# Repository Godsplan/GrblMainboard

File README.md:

GrblMainboard - v3.1
=============

A new Solution with Grbl Firmware to use cnc mills or 3d printers.

created by Christoph Kielhorn (Godsplan), Frank Herrmann (xpix)

---------------

The GrblMainboard includes the following features:

- ATMega328u (DIL Package)
- USB Connection using USB-FTDI
- Opto-Couplers for USB Connection
- ICSP-Connector for flashing the firmware
- GRBL Firmware (v0.8) and GRBL Pinout
- Connector for External Buttons for spindle, reset, etc...
- Support for four Pololu A4988 or Pololu DRV8825 Modules
- Supports dual-Y motion
- Supports cooling fan
- Supports XYZ-Limit in extra pinheader
- LED's for every axis
- LED's for every Limit
- Power LED
- AK500 Screw terminal for Steppers
- Connector for Bluetooth TTL Modules

---------------
v3.1
- Added Hall Sensor Pinout

v3.0 - GrblMainboard Backfork
- Added Pin Locations
- Added I2C Connectors for Sensors

v0.9.1 - XStepper Development

- add optional pullup resistors (1k/5V) for Hallo Sesnor switches (Cherry MP101401)
   http://www.cherrycorp.com/english/sensors/pdf/MP1014_Series.pdf

v0.9 - Initial Development

- created schema files
- created .brd

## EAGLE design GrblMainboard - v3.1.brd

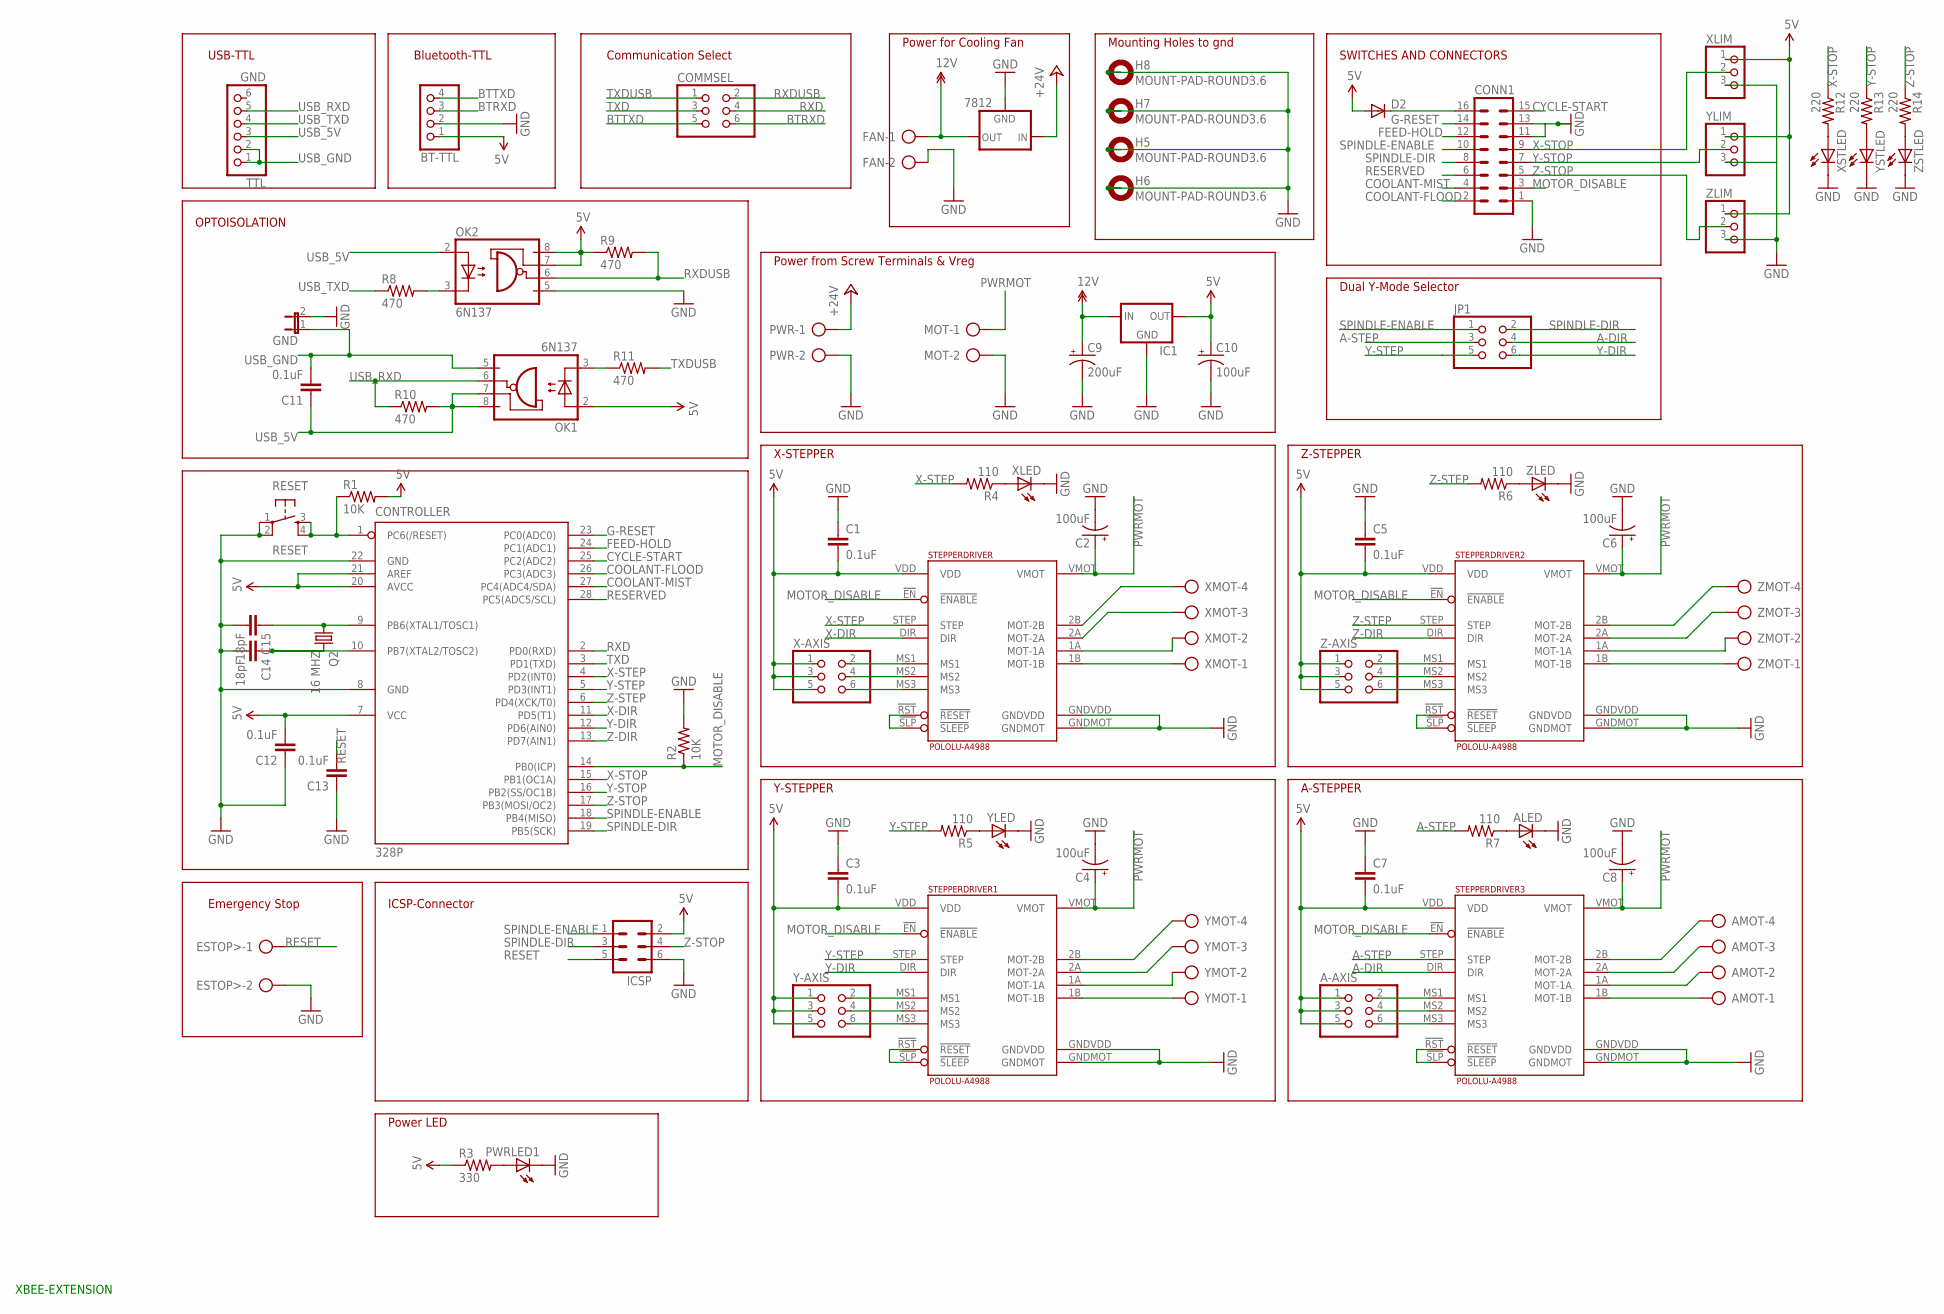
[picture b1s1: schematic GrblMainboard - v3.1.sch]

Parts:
328P: CONTROLLER; DIL28-3
7812: V_REG_78XXSINK; TO220-IGO
A-AXIS: PINHD-2X3; 2X03
ALED: LED3MM
AMOT: AK500/4
BT-TTL: PINHD-1X4; 1X04
C1, C3, C5, C7, C11, C12, C13: 0.1uF; C025-025X050
C2, C4, C6, C8: 100uF; E3,5-8
C9: 200uF; E2,5-6
C10: 100uF; E2,5-6
C14, C15: 18pF; C025-025X050
COMMSEL: PINHD-2X3; 2X03
CONN1: ML16
D2: DIODEPTH; DIODE-1N4001
ESTOP>: AK500/2
FAN: AK500/2
GND: JP1E; JP1
H5, H6, H7, H8: MOUNT-PAD-ROUND3.6; 3,6-PAD
IC1: V_REG_78XXSINK; TO220-IGO
ICSP: ML6
JP1: PINHD-2X3; 2X03
MOT: AK500/2
OK1, OK2: 6N137; DIL08
PWR: AK500/2
PWRLED1: LED3MM
Q2: 16 MHZ; HC49/S
R1, R2: 10K; AXIAL-0.3
R3: 330; 1/6W-RES
R4, R5, R6, R7: 110; AXIAL-0.3
R8, R9, R10, R11: 470; AXIAL-0.3
R12, R13, R14: 220; AXIAL-0.3
RESET: RESET; TACTILE-PTH
STEPPERDRIVER, STEPPERDRIVER1, STEPPERDRIVER2, STEPPERDRIVER3: POLOLU-A4988; POLOLU-ALLEGRO-PTH
TTL: GND; 1X06
X-AXIS: PINHD-2X3; 2X03
XLED: LED3MM
XLIM: PINHD-1X3; 1X03
XMOT: AK500/4
XSTLED: LED3MM
Y-AXIS: PINHD-2X3; 2X03
YLED: LED3MM
YLIM: PINHD-1X3; 1X03
YMOT: AK500/4
YSTLED: LED3MM
Z-AXIS: PINHD-2X3; 2X03
ZLED: LED3MM
ZLIM: PINHD-1X3; 1X03
ZMOT: AK500/4
ZSTLED: LED3MM

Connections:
5V: 328P.7 (VCC), 328P.20 (AVCC), 328P.21 (AREF), A-AXIS.1, A-AXIS.3, A-AXIS.5, BT-TTL.1, C1.2, C3.2, C5.2, C7.2, C10.+, C12.2, D2.A, IC1.OUT, ICSP.2, OK1.2 (A), OK2.7 (VE), OK2.8 (VCC), R1.P$2 (2), R3.1, R9.P$1 (1), STEPPERDRIVER.VDD, STEPPERDRIVER1.VDD, STEPPERDRIVER2.VDD, STEPPERDRIVER3.VDD, X-AXIS.1, X-AXIS.3, X-AXIS.5, XLIM.1, Y-AXIS.1, Y-AXIS.3, Y-AXIS.5, YLIM.1, Z-AXIS.1, Z-AXIS.3, Z-AXIS.5, ZLIM.1
12V: 7812.OUT, C9.+, FAN.1, IC1.IN
+24V: 7812.IN, PWR.1
A-DIR: JP1.4, STEPPERDRIVER3.DIR
A-STEP: JP1.3, R7.P$2 (2), STEPPERDRIVER3.STEP
BTRXD: BT-TTL.3, COMMSEL.6
BTTXD: BT-TTL.4, COMMSEL.5
COOLANT-FLOOD: 328P.26 (PC3(ADC3)), CONN1.2
COOLANT-MIST: 328P.27 (PC4(ADC4/SDA)), CONN1.4
CYCLE-START: 328P.25 (PC2(ADC2)), CONN1.15
FEED-HOLD: 328P.24 (PC1(ADC1)), CONN1.12
G-RESET: 328P.23 (PC0(ADC0)), CONN1.14
GND: 328P.8 (GND), 328P.22 (GND), 7812.GND, ALED.K (C), BT-TTL.2, C1.1, C2.-, C3.1, C4.-, C5.1, C6.-, C7.1, C8.-, C9.-, C10.-, C12.1, C13.1, C14.2, C15.2, CONN1.1, CONN1.11, CONN1.13, ESTOP>.2, FAN.2, GND.2, H5.B3,6, H6.B3,6, H7.B3,6, H8.B3,6, IC1.GND, ICSP.6, MOT.2, OK2.5 (GND), PWR.2, PWRLED1.K (C), R2.P$2 (2), RESET.1, RESET.2, STEPPERDRIVER.GNDMOT, STEPPERDRIVER.GNDVDD, STEPPERDRIVER1.GNDMOT, STEPPERDRIVER1.GNDVDD, STEPPERDRIVER2.GNDMOT, STEPPERDRIVER2.GNDVDD, STEPPERDRIVER3.GNDMOT, STEPPERDRIVER3.GNDVDD, XLED.K (C), XLIM.3, XSTLED.K (C), YLED.K (C), YLIM.3, YSTLED.K (C), ZLED.K (C), ZLIM.3, ZSTLED.K (C)
MOTOR_DISABLE: 328P.14 (PB0(ICP)), CONN1.3, R2.P$1 (1), STEPPERDRIVER.!EN (!ENABLE), STEPPERDRIVER1.!EN (!ENABLE), STEPPERDRIVER2.!EN (!ENABLE), STEPPERDRIVER3.!EN (!ENABLE)
unnamed: STEPPERDRIVER.1B (MOT-1B), XMOT.1
unnamed: STEPPERDRIVER.1A (MOT-1A), XMOT.2
unnamed: STEPPERDRIVER.2A (MOT-2A), XMOT.3
unnamed: STEPPERDRIVER.2B (MOT-2B), XMOT.4
unnamed: STEPPERDRIVER.!RST (!RESET), STEPPERDRIVER.!SLP (!SLEEP)
unnamed: STEPPERDRIVER.MS1, X-AXIS.2
unnamed: STEPPERDRIVER.MS2, X-AXIS.4
unnamed: STEPPERDRIVER.MS3, X-AXIS.6
unnamed: STEPPERDRIVER1.1B (MOT-1B), YMOT.1
unnamed: STEPPERDRIVER1.1A (MOT-1A), YMOT.2
unnamed: STEPPERDRIVER1.2A (MOT-2A), YMOT.3
unnamed: STEPPERDRIVER1.2B (MOT-2B), YMOT.4
unnamed: STEPPERDRIVER1.!RST (!RESET), STEPPERDRIVER1.!SLP (!SLEEP)
unnamed: STEPPERDRIVER1.MS1, Y-AXIS.2
unnamed: STEPPERDRIVER1.MS2, Y-AXIS.4
unnamed: STEPPERDRIVER1.MS3, Y-AXIS.6
unnamed: STEPPERDRIVER2.2B (MOT-2B), ZMOT.4
unnamed: STEPPERDRIVER2.2A (MOT-2A), ZMOT.3
unnamed: STEPPERDRIVER2.1A (MOT-1A), ZMOT.2
unnamed: STEPPERDRIVER2.1B (MOT-1B), ZMOT.1
unnamed: STEPPERDRIVER2.!RST (!RESET), STEPPERDRIVER2.!SLP (!SLEEP)
unnamed: STEPPERDRIVER2.MS1, Z-AXIS.2
unnamed: STEPPERDRIVER2.MS2, Z-AXIS.4
unnamed: STEPPERDRIVER2.MS3, Z-AXIS.6
unnamed: AMOT.1, STEPPERDRIVER3.1B (MOT-1B)
unnamed: AMOT.2, STEPPERDRIVER3.1A (MOT-1A)
unnamed: AMOT.3, STEPPERDRIVER3.2A (MOT-2A)
unnamed: AMOT.4, STEPPERDRIVER3.2B (MOT-2B)
unnamed: STEPPERDRIVER3.!RST (!RESET), STEPPERDRIVER3.!SLP (!SLEEP)
unnamed: A-AXIS.2, STEPPERDRIVER3.MS1
unnamed: A-AXIS.4, STEPPERDRIVER3.MS2
unnamed: A-AXIS.6, STEPPERDRIVER3.MS3
unnamed: 328P.9 (PB6(XTAL1/TOSC1)), C15.1, Q2.1
unnamed: 328P.10 (PB7(XTAL2/TOSC2)), C14.1, Q2.2
unnamed: OK2.3 (C), R8.P$2 (2)
unnamed: OK1.3 (C), R11.P$1 (1)
unnamed: R12.P$2 (2), XSTLED.A
unnamed: R4.P$1 (1), XLED.A
unnamed: R5.P$1 (1), YLED.A
unnamed: R6.P$1 (1), ZLED.A
unnamed: ALED.A, R7.P$1 (1)
unnamed: R13.P$2 (2), YSTLED.A
unnamed: PWRLED1.A, R3.2
unnamed: R14.P$2 (2), ZSTLED.A
unnamed: CONN1.16, D2.C
PWRMOT: C2.+, C4.+, C6.+, C8.+, MOT.1, STEPPERDRIVER.VMOT, STEPPERDRIVER1.VMOT, STEPPERDRIVER2.VMOT, STEPPERDRIVER3.VMOT
RESERVED: 328P.28 (PC5(ADC5/SCL)), CONN1.6
RESET: 328P.1 (PC6(/RESET)), C13.2, ESTOP>.1, ICSP.5, R1.P$1 (1), RESET.3, RESET.4
RXD: 328P.2 (PD0(RXD)), COMMSEL.4
RXDUSB: COMMSEL.2, OK2.6 (VO), R9.P$2 (2)
SPINDLE-DIR: 328P.19 (PB5(SCK)), CONN1.8, ICSP.3, JP1.2
SPINDLE-ENABLE: 328P.18 (PB4(MISO)), CONN1.10, ICSP.1, JP1.1
TXD: 328P.3 (PD1(TXD)), COMMSEL.3
TXDUSB: COMMSEL.1, R11.P$2 (2)
USB_5V: C11.1, OK1.7 (VE), OK1.8 (VCC), OK2.2 (A), R10.P$2 (2), TTL.3
USB_GND: C11.2, GND.1, OK1.5 (GND), TTL.1, TTL.2
USB_RXD: OK1.6 (VO), R10.P$1 (1), TTL.5
USB_TXD: R8.P$1 (1), TTL.4
X-DIR: 328P.11 (PD5(T1)), STEPPERDRIVER.DIR
X-STEP: 328P.4 (PD2(INT0)), R4.P$2 (2), STEPPERDRIVER.STEP
X-STOP: 328P.15 (PB1(OC1A)), CONN1.9, R12.P$1 (1), XLIM.2
Y-DIR: 328P.12 (PD6(AIN0)), JP1.6, STEPPERDRIVER1.DIR
Y-STEP: 328P.5 (PD3(INT1)), JP1.5, R5.P$2 (2), STEPPERDRIVER1.STEP
Y-STOP: 328P.16 (PB2(SS/OC1B)), CONN1.7, R13.P$1 (1), YLIM.2
Z-DIR: 328P.13 (PD7(AIN1)), STEPPERDRIVER2.DIR
Z-STEP: 328P.6 (PD4(XCK/T0)), R6.P$2 (2), STEPPERDRIVER2.STEP
Z-STOP: 328P.17 (PB3(MOSI/OC2)), CONN1.5, ICSP.4, R14.P$1 (1), ZLIM.2

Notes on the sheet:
X-STEPPER
Y-STEPPER
Z-STEPPER
Power from Screw Terminals & Vreg
A-STEPPER
Dual Y-Mode Selector
OPTOISOLATION
Power for Cooling Fan
ICSP-Connector
Mounting Holes to gnd
XBEE-EXTENSION
USB-TTL
SWITCHES AND CONNECTORS
Power LED
Bluetooth-TTL
Emergency Stop
Communication Select

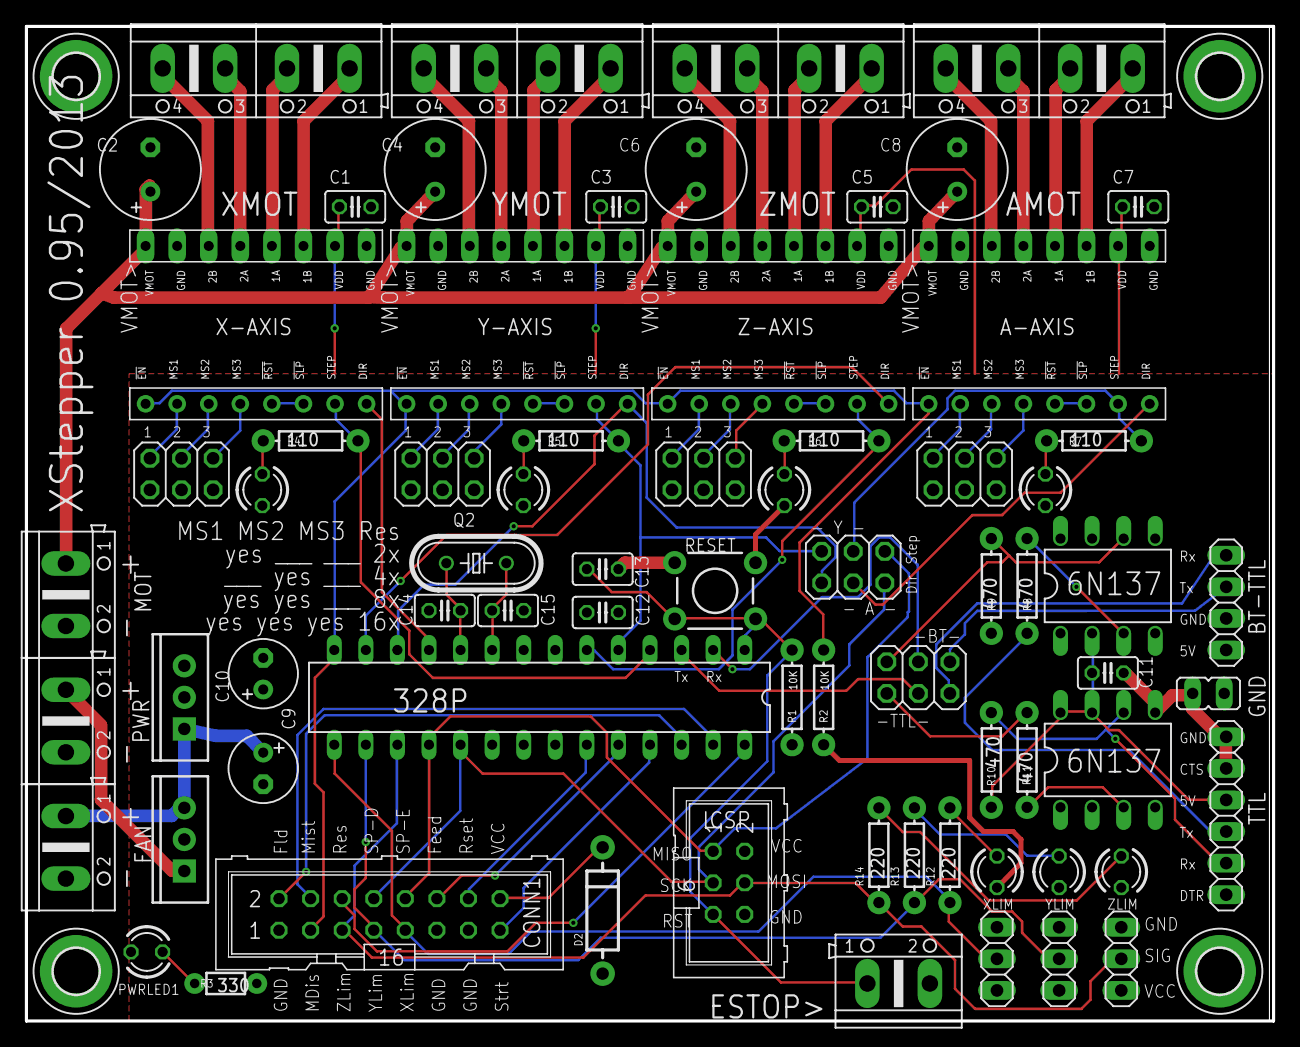
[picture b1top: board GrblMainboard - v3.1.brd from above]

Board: 2 copper layers, 100.3 x 80.0 mm, 75 parts (0 on the bottom side), 81 nets.

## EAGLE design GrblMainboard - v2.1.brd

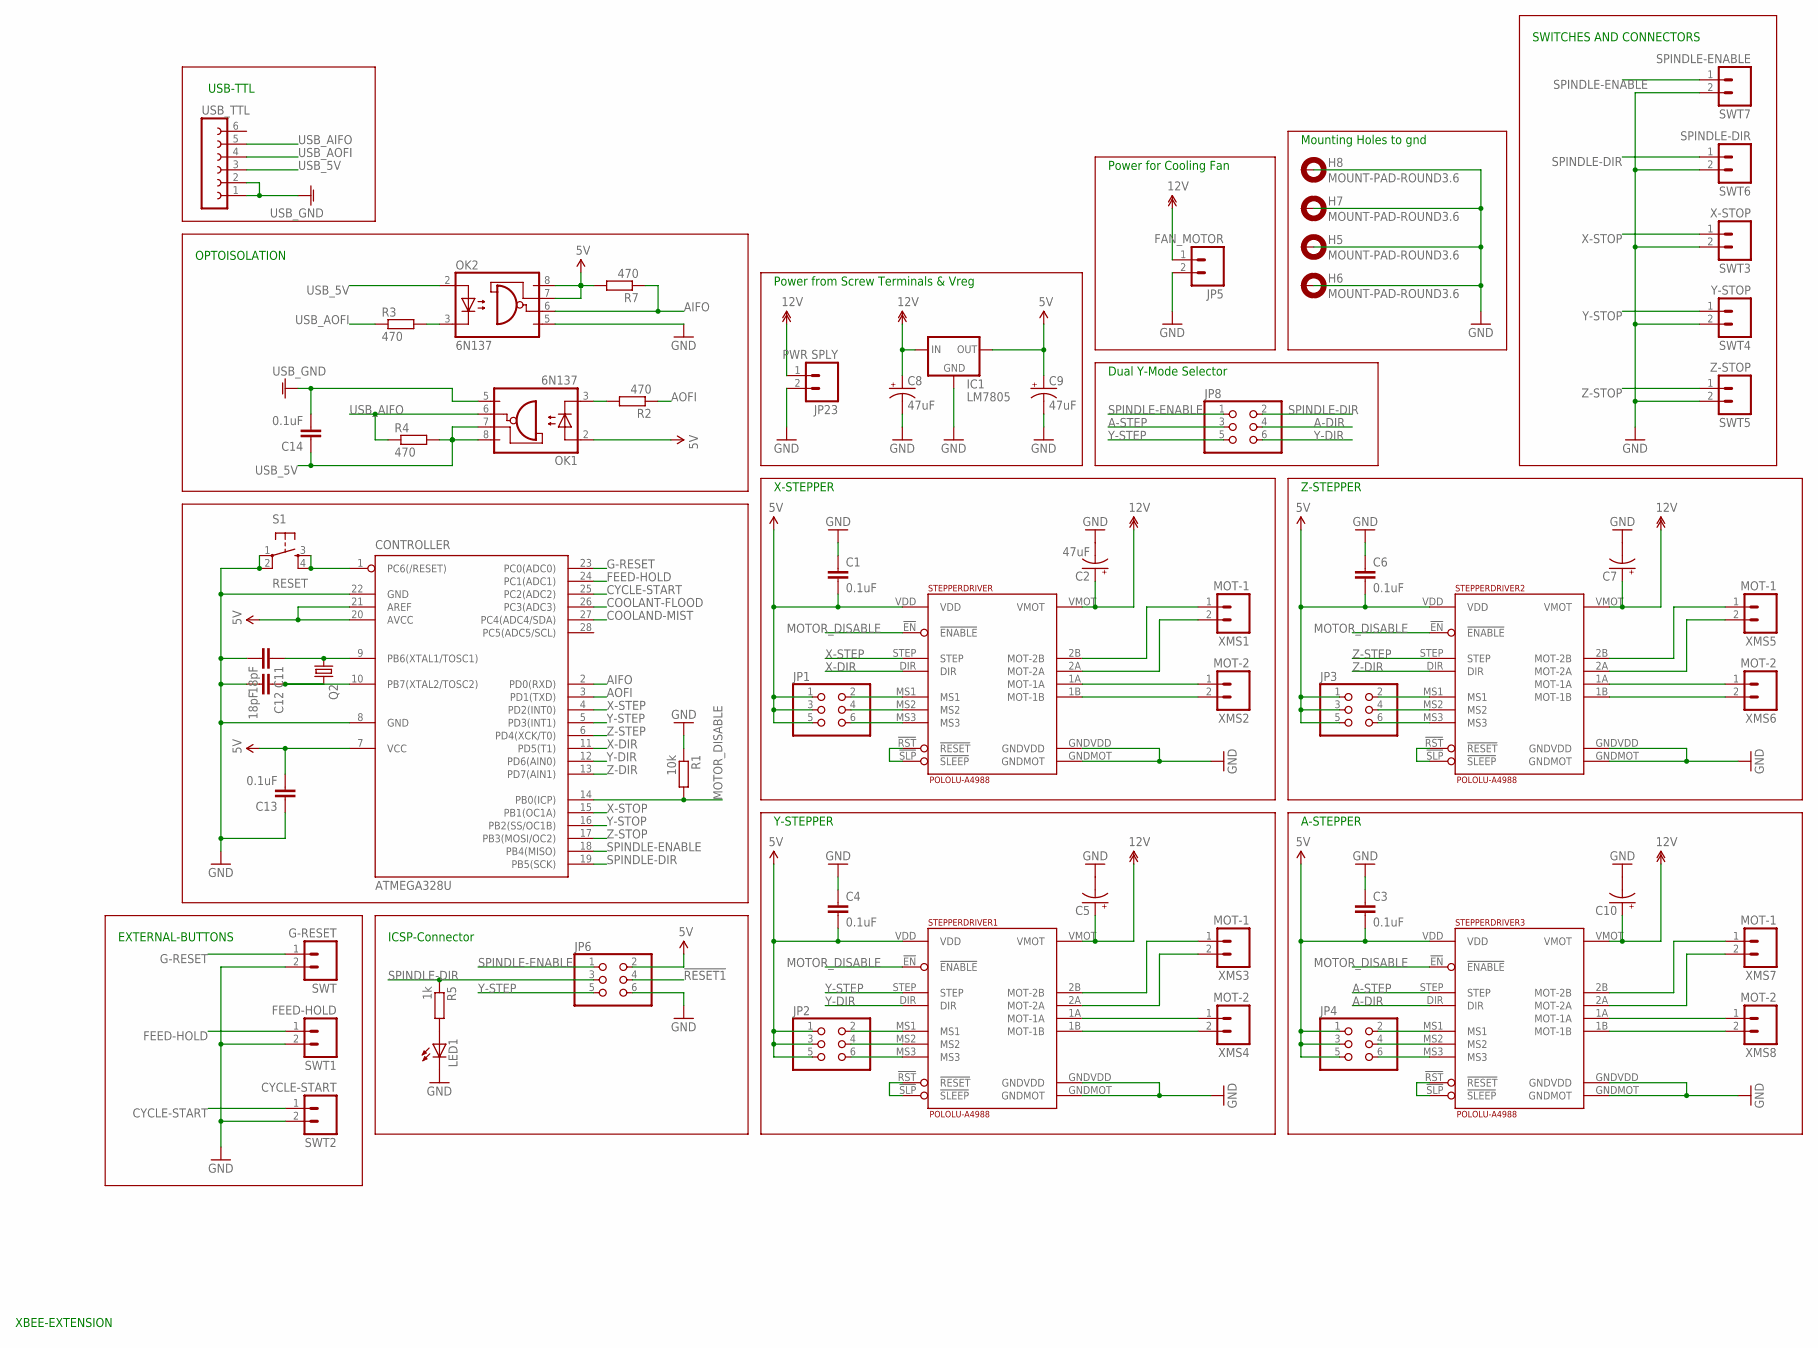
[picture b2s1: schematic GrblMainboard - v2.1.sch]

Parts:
ATMEGA328U: CONTROLLER; DIL28-3
C1, C3, C4, C6: 0.1uF; C025-025X050
C2, C8, C9: 47uF; E2,5-6
C5, C7, C10: CPOL-USE2.5-6; E2,5-6
C11, C12: 18pF; CAP-PTH-SMALL2
C13, C14: 0.1uF; CAP-PTH-SMALL2
H5, H6, H7, H8: MOUNT-PAD-ROUND3.6; 3,6-PAD
IC1: LM7805; 78XXL-CUSTOM
JP1, JP2, JP3, JP4, JP6, JP8: PINHD-2X3; 2X03
JP5: FAN_MOTOR; SCREWTERMINAL-5MM-2
JP23: PWR SPLY; SCREWTERMINAL-5MM-2
LED1: LED5MM
OK1, OK2: 6N137; DIL08
Q2: CRYSTALHC49S; HC49/S
R1: 10k; 0207/10
R2, R3, R4, R7: 470; 0207/12
R5: 1k; 0207/10
S1: RESET; TACTILE-PTH
STEPPERDRIVER, STEPPERDRIVER1, STEPPERDRIVER2, STEPPERDRIVER3: POLOLU-A4988; POLOLU-ALLEGRO-PTH
SWT: G-RESET; SCREWTERMINAL-5MM-2
SWT1: FEED-HOLD; SCREWTERMINAL-5MM-2
SWT2: CYCLE-START; SCREWTERMINAL-5MM-2
SWT3: X-STOP; SCREWTERMINAL-5MM-2
SWT4: Y-STOP; SCREWTERMINAL-5MM-2
SWT5: Z-STOP; SCREWTERMINAL-5MM-2
SWT6: SPINDLE-DIR; SCREWTERMINAL-5MM-2
SWT7: SPINDLE-ENABLE; SCREWTERMINAL-5MM-2
USB_TTL: FE06-1; FE06
XMS1, XMS3, XMS5, XMS7: MOT-1; SCREWTERMINAL-5MM-2
XMS2, XMS4, XMS6, XMS8: MOT-2; SCREWTERMINAL-5MM-2

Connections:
5V: ATMEGA328U.7 (VCC), ATMEGA328U.20 (AVCC), ATMEGA328U.21 (AREF), C1.2, C3.2, C4.2, C6.2, C9.+, C13.2, IC1.OUT, JP1.1, JP1.3, JP1.5, JP2.1, JP2.3, JP2.5, JP3.1, JP3.3, JP3.5, JP4.1, JP4.3, JP4.5, JP6.2, OK1.2 (A), OK2.7 (VE), OK2.8 (VCC), R7.2, STEPPERDRIVER.VDD, STEPPERDRIVER1.VDD, STEPPERDRIVER2.VDD, STEPPERDRIVER3.VDD
12V: C2.+, C5.+, C7.+, C8.+, C10.+, IC1.IN, JP5.1, JP23.1, STEPPERDRIVER.VMOT, STEPPERDRIVER1.VMOT, STEPPERDRIVER2.VMOT, STEPPERDRIVER3.VMOT
!RESET1: ATMEGA328U.1 (PC6(/RESET)), JP6.4, S1.3, S1.4
A-DIR: JP8.4, STEPPERDRIVER3.DIR
A-STEP: JP8.3, STEPPERDRIVER3.STEP
AIFO: ATMEGA328U.2 (PD0(RXD)), OK2.6 (VO), R7.1
AOFI: ATMEGA328U.3 (PD1(TXD)), R2.1
COOLAND-MIST: ATMEGA328U.27 (PC4(ADC4/SDA))
COOLANT-FLOOD: ATMEGA328U.26 (PC3(ADC3))
CYCLE-START: ATMEGA328U.25 (PC2(ADC2)), SWT2.1
FEED-HOLD: ATMEGA328U.24 (PC1(ADC1)), SWT1.1
G-RESET: ATMEGA328U.23 (PC0(ADC0)), SWT.1
GND: ATMEGA328U.8 (GND), ATMEGA328U.22 (GND), C1.1, C2.-, C3.1, C4.1, C5.-, C6.1, C7.-, C8.-, C9.-, C10.-, C11.2, C12.2, C13.1, IC1.GND, JP5.2, JP6.6, JP23.2, LED1.K (C), OK2.5 (GND), R1.1, S1.1, S1.2, STEPPERDRIVER.GNDMOT, STEPPERDRIVER.GNDVDD, STEPPERDRIVER1.GNDMOT, STEPPERDRIVER1.GNDVDD, STEPPERDRIVER2.GNDMOT, STEPPERDRIVER2.GNDVDD, STEPPERDRIVER3.GNDMOT, STEPPERDRIVER3.GNDVDD, SWT.2, SWT1.2, SWT2.2, SWT3.2, SWT4.2, SWT5.2, SWT6.2, SWT7.2
GNDA: C14.2, OK1.5 (GND), USB_TTL.1, USB_TTL.2
MOTOR_DISABLE: ATMEGA328U.14 (PB0(ICP)), R1.2, STEPPERDRIVER.!EN (!ENABLE), STEPPERDRIVER1.!EN (!ENABLE), STEPPERDRIVER2.!EN (!ENABLE), STEPPERDRIVER3.!EN (!ENABLE)
unnamed: STEPPERDRIVER.2B (MOT-2B), XMS1.1
unnamed: STEPPERDRIVER.2A (MOT-2A), XMS1.2
unnamed: STEPPERDRIVER.1A (MOT-1A), XMS2.1
unnamed: STEPPERDRIVER.1B (MOT-1B), XMS2.2
unnamed: STEPPERDRIVER.!RST (!RESET), STEPPERDRIVER.!SLP (!SLEEP)
unnamed: JP1.2, STEPPERDRIVER.MS1
unnamed: JP1.4, STEPPERDRIVER.MS2
unnamed: JP1.6, STEPPERDRIVER.MS3
unnamed: STEPPERDRIVER1.2B (MOT-2B), XMS3.1
unnamed: STEPPERDRIVER1.2A (MOT-2A), XMS3.2
unnamed: STEPPERDRIVER1.1A (MOT-1A), XMS4.1
unnamed: STEPPERDRIVER1.1B (MOT-1B), XMS4.2
unnamed: STEPPERDRIVER1.!RST (!RESET), STEPPERDRIVER1.!SLP (!SLEEP)
unnamed: JP2.2, STEPPERDRIVER1.MS1
unnamed: JP2.4, STEPPERDRIVER1.MS2
unnamed: JP2.6, STEPPERDRIVER1.MS3
unnamed: STEPPERDRIVER2.2B (MOT-2B), XMS5.1
unnamed: STEPPERDRIVER2.2A (MOT-2A), XMS5.2
unnamed: STEPPERDRIVER2.1A (MOT-1A), XMS6.1
unnamed: STEPPERDRIVER2.1B (MOT-1B), XMS6.2
unnamed: STEPPERDRIVER2.!RST (!RESET), STEPPERDRIVER2.!SLP (!SLEEP)
unnamed: JP3.2, STEPPERDRIVER2.MS1
unnamed: JP3.4, STEPPERDRIVER2.MS2
unnamed: JP3.6, STEPPERDRIVER2.MS3
unnamed: STEPPERDRIVER3.2B (MOT-2B), XMS7.1
unnamed: STEPPERDRIVER3.2A (MOT-2A), XMS7.2
unnamed: STEPPERDRIVER3.1A (MOT-1A), XMS8.1
unnamed: STEPPERDRIVER3.1B (MOT-1B), XMS8.2
unnamed: STEPPERDRIVER3.!RST (!RESET), STEPPERDRIVER3.!SLP (!SLEEP)
unnamed: JP4.2, STEPPERDRIVER3.MS1
unnamed: JP4.4, STEPPERDRIVER3.MS2
unnamed: JP4.6, STEPPERDRIVER3.MS3
unnamed: ATMEGA328U.9 (PB6(XTAL1/TOSC1)), C11.1, Q2.1
unnamed: ATMEGA328U.10 (PB7(XTAL2/TOSC2)), C12.1, Q2.2
unnamed: OK2.3 (C), R3.2
unnamed: OK1.3 (C), R2.2
unnamed: LED1.A, R5.2
SPINDLE-DIR: ATMEGA328U.19 (PB5(SCK)), JP6.3, JP8.2, R5.1, SWT6.1
SPINDLE-ENABLE: ATMEGA328U.18 (PB4(MISO)), JP6.1, JP8.1, SWT7.1
USB_5V: C14.1, OK1.7 (VE), OK1.8 (VCC), OK2.2 (A), R4.2, USB_TTL.3
USB_AIFO: OK1.6 (VO), R4.1, USB_TTL.5
USB_AOFI: R3.1, USB_TTL.4
X-DIR: ATMEGA328U.11 (PD5(T1)), STEPPERDRIVER.DIR
X-STEP: ATMEGA328U.4 (PD2(INT0)), STEPPERDRIVER.STEP
X-STOP: ATMEGA328U.15 (PB1(OC1A)), SWT3.1
Y-DIR: ATMEGA328U.12 (PD6(AIN0)), JP8.6, STEPPERDRIVER1.DIR
Y-STEP: ATMEGA328U.5 (PD3(INT1)), JP6.5, JP8.5, STEPPERDRIVER1.STEP
Y-STOP: ATMEGA328U.16 (PB2(SS/OC1B)), SWT4.1
Z-DIR: ATMEGA328U.13 (PD7(AIN1)), STEPPERDRIVER2.DIR
Z-STEP: ATMEGA328U.6 (PD4(XCK/T0)), STEPPERDRIVER2.STEP
Z-STOP: ATMEGA328U.17 (PB3(MOSI/OC2)), SWT5.1

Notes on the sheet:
X-STEPPER
Y-STEPPER
Z-STEPPER
Power from Screw Terminals & Vreg
A-STEPPER
Dual Y-Mode Selector
OPTOISOLATION
Power for Cooling Fan
ICSP-Connector
Mounting Holes to gnd
XBEE-EXTENSION
EXTERNAL-BUTTONS
USB-TTL
SWITCHES AND CONNECTORS

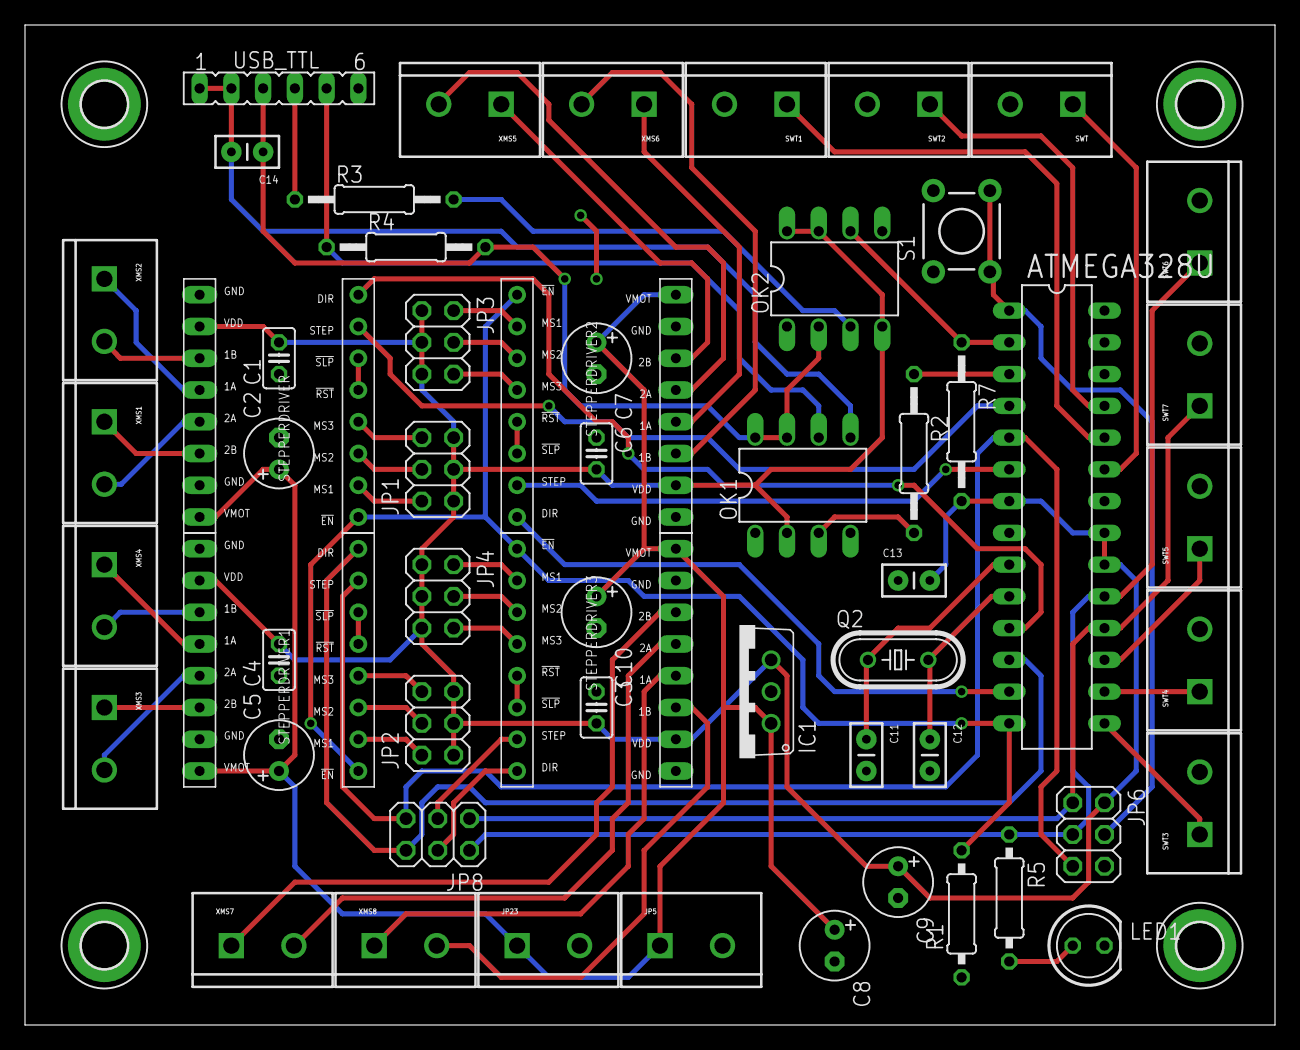
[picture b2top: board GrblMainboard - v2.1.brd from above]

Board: 2 copper layers, 100.0 x 80.0 mm, 60 parts (0 on the bottom side), 64 nets.

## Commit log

2013-03-02 first
2013-03-02 cleaning
2013-03-07 Power wires thicker for ~ 3A
    - make power wires thicker
    - check for error in DRU schema and board
    - replace Atmega328U with Atmega328
2013-03-08 added mounting holes for CPU Fan
    i added 4 holes to add a 12V CPU Fan
2013-03-20 Add pullup Resistor for Atmel Reset pin
2013-03-26 Add screw terminal for reset button
    also change the central capacitors for a better place.
2013-03-26 delete unused files
    sorry ;)
2013-09-08 Backfork from XStepper
2013-09-08 cleaning and moving
2013-09-08 added hall sensor pin

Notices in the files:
parts and their libraries:
SparkFun-Aesthetics: Licensing: CC v3.0 Share-Alike You are welcome to use this library for commercial purposes.
